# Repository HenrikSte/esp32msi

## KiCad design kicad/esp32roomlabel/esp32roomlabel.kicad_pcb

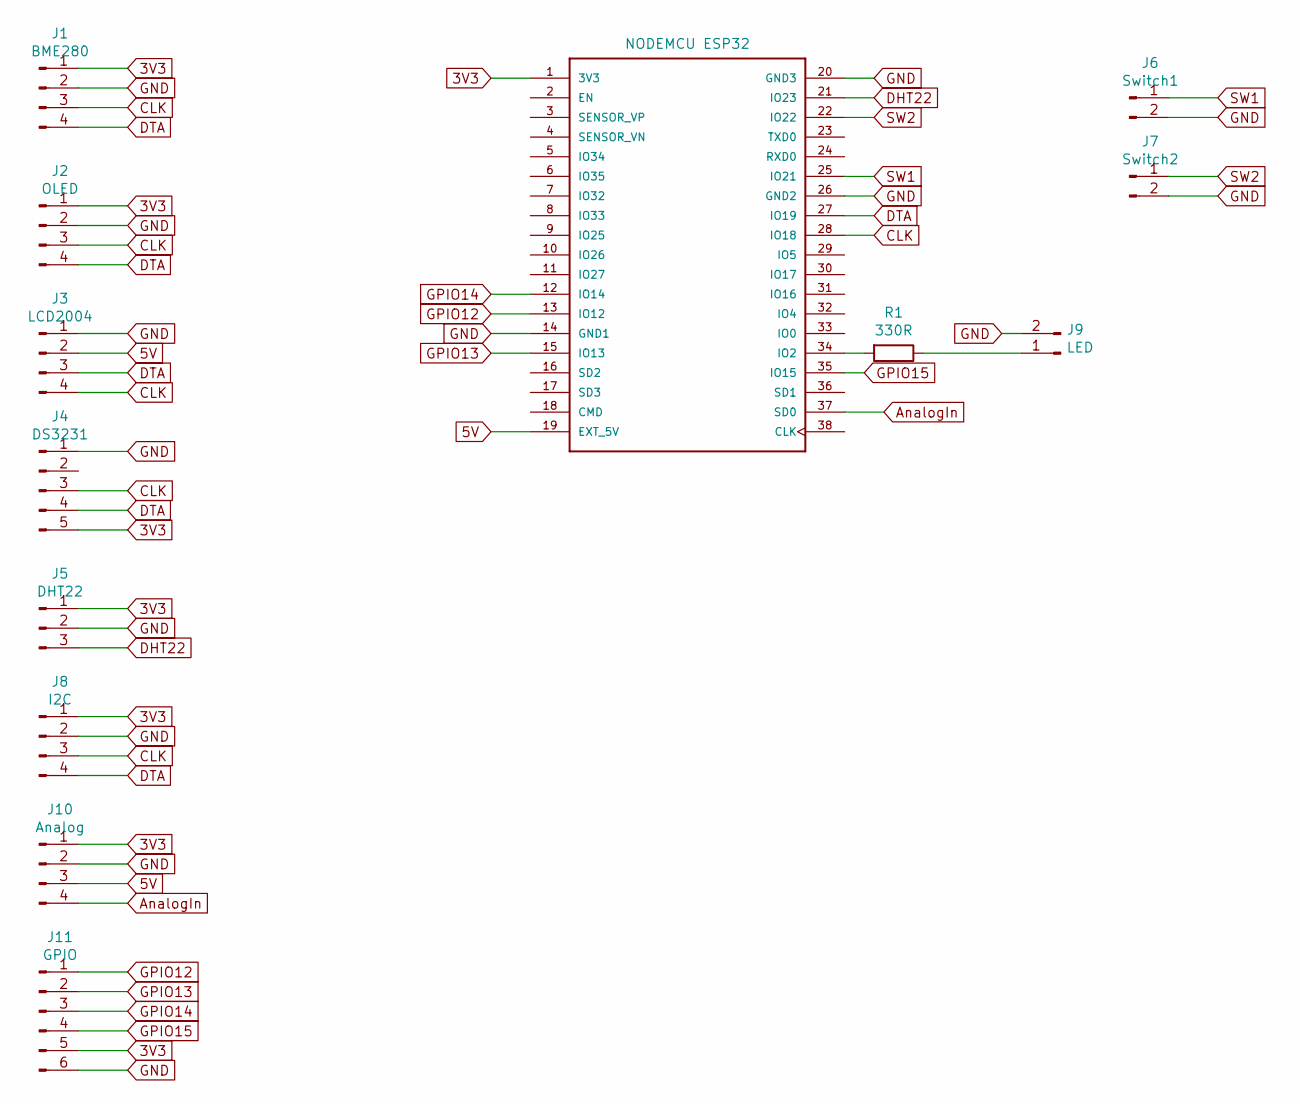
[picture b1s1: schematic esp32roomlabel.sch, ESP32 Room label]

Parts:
J1: BME280; PinHeader_1x04_P2.54mm_Vertical
J2: OLED; PinHeader_1x04_P2.54mm_Vertical
J3: LCD2004; PinHeader_1x04_P2.54mm_Vertical
J4: DS3231; PinHeader_1x05_P2.54mm_Vertical
J5: DHT22; PinHeader_1x03_P2.54mm_Vertical
J6: Switch1; PinHeader_1x02_P2.54mm_Vertical
J7: Switch2; PinHeader_1x02_P2.54mm_Vertical
J8: I2C; PinHeader_1x04_P2.54mm_Vertical
J9: LED; PinHeader_1x02_P2.54mm_Vertical
J10: Analog; PinHeader_1x04_P2.54mm_Vertical
J11: GPIO; PinHeader_1x06_P2.54mm_Vertical
R1: 330R; R_Axial_DIN0204_L3.6mm_D1.6mm_P5.08mm_Horizontal
U1: NODEMCU ESP32; MODULE_ESP32-DEVKITC-32D

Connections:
3V3: J1.1, J2.1, J4.5, J5.1, J8.1, J10.1, J11.5, U1.1 (3V3)
5V: J3.2, J10.3, U1.19 (EXT_5V)
AnalogIn: J10.4, U1.37 (SD0)
CLK: J1.3, J2.3, J3.4, J4.3, J8.3, U1.28 (IO18)
DHT22: J5.3, U1.21 (IO23)
DTA: J1.4, J2.4, J3.3, J4.4, J8.4, U1.27 (IO19)
GND: J1.2, J2.2, J3.1, J4.1, J5.2, J6.2, J7.2, J8.2, J9.2, J10.2, J11.6, U1.14 (GND1), U1.20 (GND3), U1.26 (GND2)
GPIO12: J11.1, U1.13 (IO12)
GPIO13: J11.2, U1.15 (IO13)
GPIO14: J11.3, U1.12 (IO14)
GPIO15: J11.4, U1.35 (IO15)
unnamed: J9.1, R1.1
unnamed: R1.2, U1.34 (IO2)
SW1: J6.1, U1.25 (IO21)
SW2: J7.1, U1.22 (IO22)

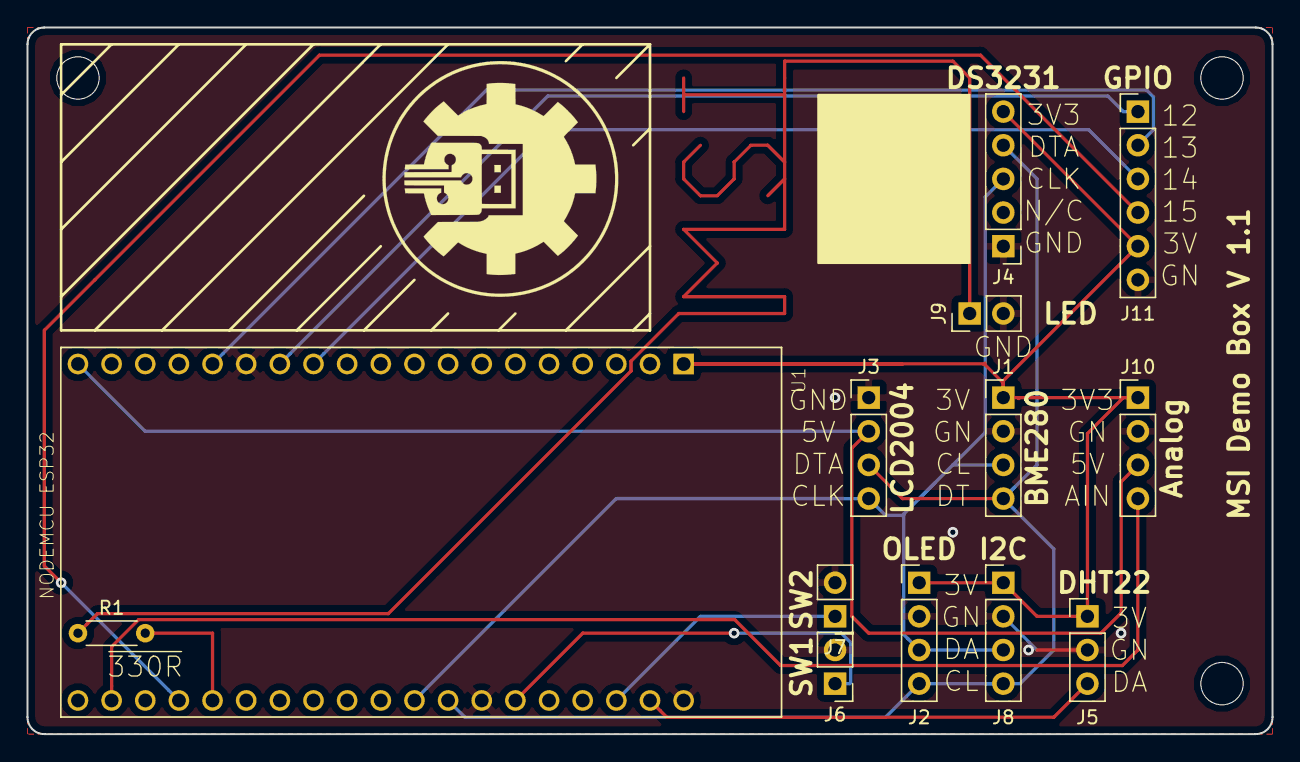
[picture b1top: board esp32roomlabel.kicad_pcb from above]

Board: 2 copper layers, 94.0 x 53.3 mm, 13 parts (0 on the bottom side), 15 nets.

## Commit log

2019-09-10 Autoconnect and Exceptions
2019-09-11 included TrueRandom lib in project
2019-09-12 Updated PCB
    Added GPIO and Analog pin header
2019-10-10 optional parameters update for MSI 1.3
2019-11-13 Bulk message sending added
    added 2 messages: One to request a number of messages and the other is the actual message that will be sent n times.
2021-11-03 Basic work for photometer
